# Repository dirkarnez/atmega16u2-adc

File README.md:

atmega16u2-adc
==============
- https://github.com/dirkarnez/ringbuffer
- https://github.com/dirkarnez/lufa-playground

### Datasheet
- https://ww1.microchip.com/downloads/en/DeviceDoc/doc7799.pdf

### Notes
- [Gammon Forum : Electronics : Microprocessors : How to make an Arduino-compatible minimal board](https://www.gammon.com.au/forum/?id=11637)
- [Gammon Forum : Electronics : Microprocessors : Minimal circuit for Atmega328 processor (shows wire-wrapping)](https://www.gammon.com.au/forum/?id=11109)
- `avrdude -p m328p -P /dev/ttyACM0 -c avrisp -b 19200 -U flash:w:release.hex`
- `"%LOCALAPPDATA%\Arduino15\packages\arduino\tools\avrdude\6.3.0-arduino17/bin/avrdude" "-C%LOCALAPPDATA%\Arduino15\packages\arduino\tools\avrdude\6.3.0-arduino17/etc/avrdude.conf" -v -p m16u2 -c arduino -PCOM5 -b19200 -U flash:w:Keyboard.hex:i -F -D`
- datasheet
  - `PDO, SPI Serial Programming Data Output. During Serial Program Downloading, this pin is used as data output line for the AT90USB82/162. `

### Bootloader
- [Pro Micro & Fio V3 Hookup Guide - SparkFun Learn](https://learn.sparkfun.com/tutorials/pro-micro--fio-v3-hookup-guide/troubleshooting-and-faq)
- [Installing an Arduino Bootloader - SparkFun Learn](https://learn.sparkfun.com/tutorials/installing-an-arduino-bootloader)
### Reference
- [Arduino入門教學(17) – 如何用 Arduino 燒錄 AVR 晶片 (作者：Cooper Maa)](http://programmermagazine.github.io/201405/htm/article1.html)
- [**Arduino 烧录 Boot Loader | 米米的博客**](https://zhangshuqiao.org/2019-10/Arduino%E7%83%A7%E5%BD%95Boot%20Loader/)
- [analogRead() - Arduino Reference](https://www.arduino.cc/reference/en/language/functions/analog-io/analogread/)
- https://github.com/arduino/ArduinoCore-avr/blob/master/firmwares/atmegaxxu2/arduino-usbserial/Arduino-usbserial-atmega16u2-Uno-Rev3.hex
  - `avrdude -p at90usb82 -F -P usb -c avrispmkii -U flash:w:UNO-dfu_and_usbserial_combined.hex -U lfuse:w:0xFF:m -U hfuse:w:0xD9:m -U efuse:w:0xF4:m -U lock:w:0x0F:m`
- https://github.com/arduino/ArduinoCore-avr/tree/master/firmwares/arduinoISP
  - https://github.com/arduino/ArduinoCore-avr/tree/master/firmwares/atmegaxxu2
- [用 AVR 做 USB 應用的考察 | Kalan's Blog](https://blog.kalan.dev/posts/2021-11-24-avr-usb-capability)
- [Arduino ATmega16U2 编译 LUFA_arduino mega16u2 源码-CSDN博客](https://blog.csdn.net/wowocpp/article/details/80626065)

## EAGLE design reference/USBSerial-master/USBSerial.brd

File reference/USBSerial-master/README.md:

# Freetronics USB to Serial converter

Can also be used as an atmega16u2 breakout/development board.

For full details see [http://freetronics.com/usbserial](http://freetronics.com/usbserial)

[View Schematic as PDF](https://github.com/freetronics/USBSerial/raw/master/USBSerial.pdf)

Design (C) 2013 Freetronics Pty Ltd
Published under the [TAPR Open Hardware License](http://tapr.org/ohl)

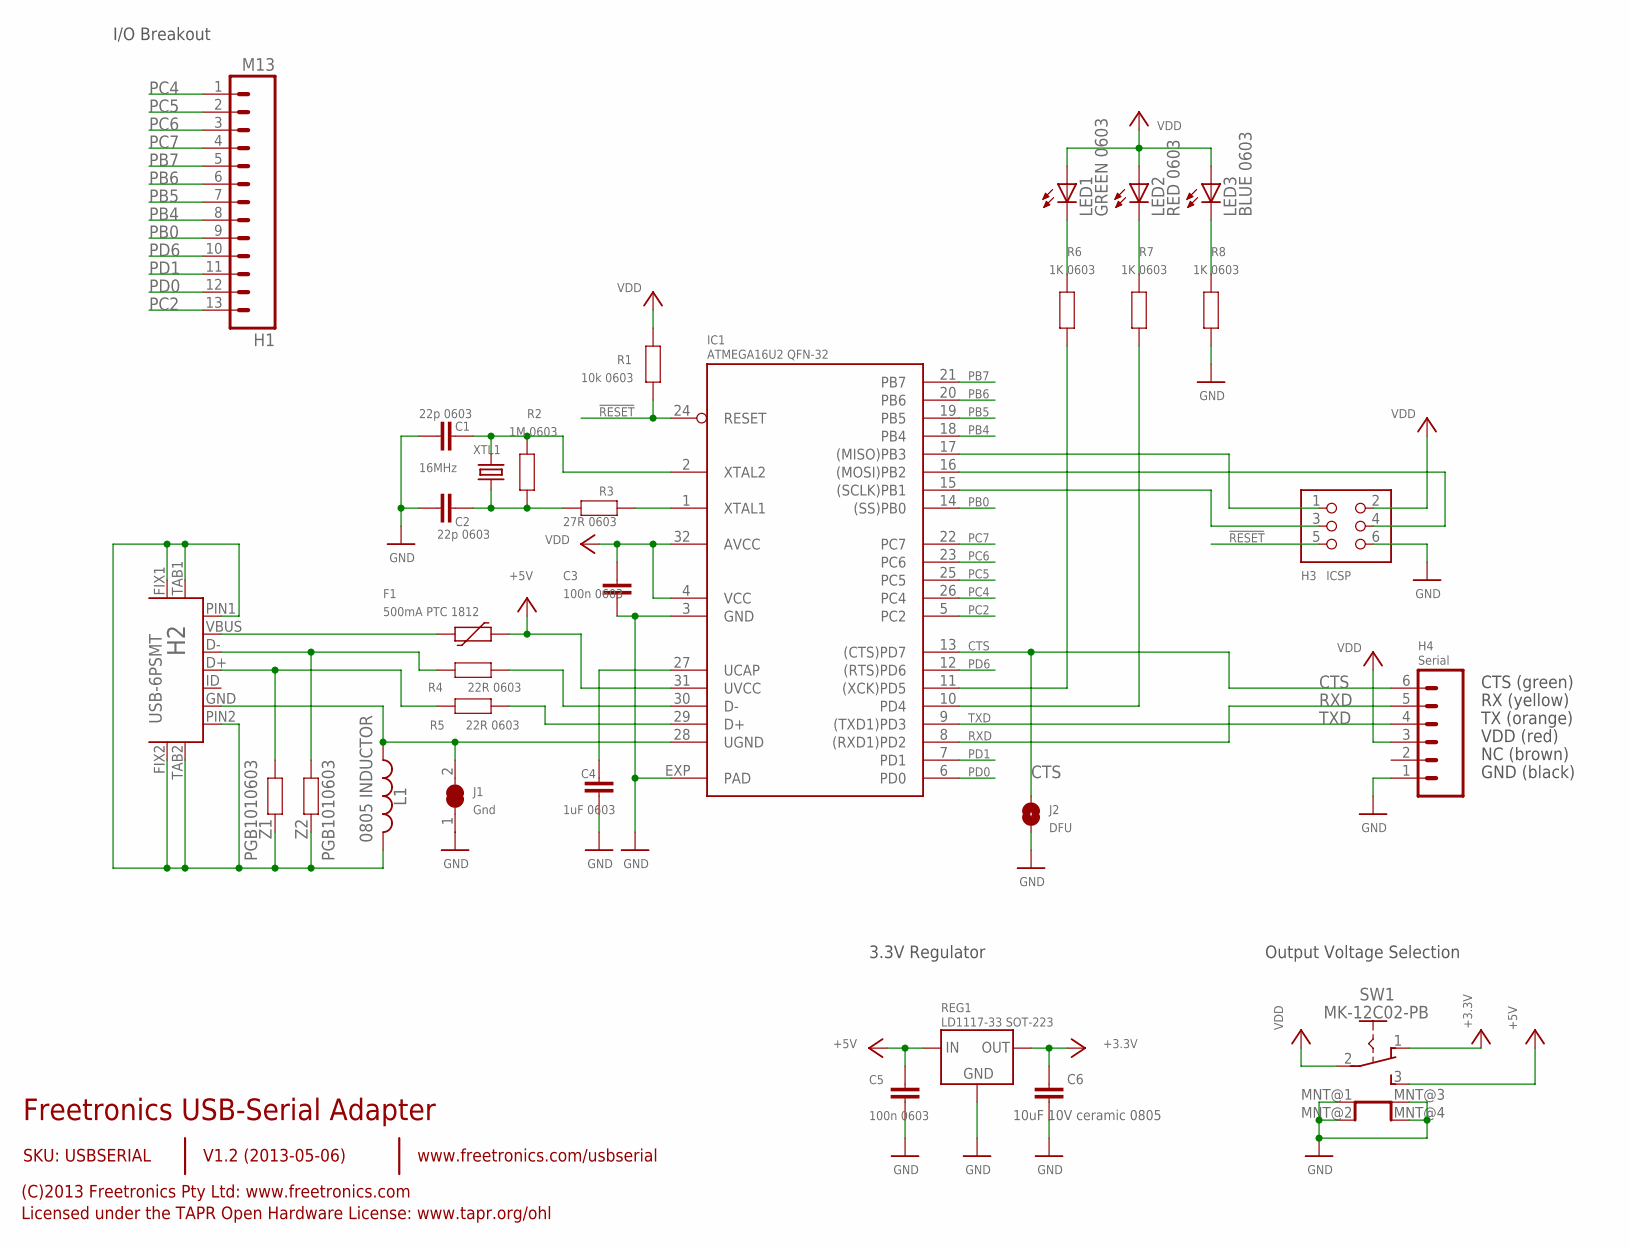
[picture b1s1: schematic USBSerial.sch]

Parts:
C1, C2: 22p 0603; 0603
C3, C5: 100n 0603; 0603
C4: 1uF 0603; 0603
C6: 10uF 10V ceramic 0805; C0805
F1: 500mA PTC 1812; 1812
H1: M13; 1X13
H2: USB-6PSMT; USB-MICROB-MB05PMXX
H3: ICSP; HEADER_2X3
H4: Serial; 1X06
IC1: ATMEGA16U2 QFN-32; ATMEL_QFN32
J1: Gnd; SJC
J2: DFU; SJ
L1: 0805 INDUCTOR; 0805-LARGE
LED1: GREEN 0603; LED-0603
LED2: RED 0603; LED-0603
LED3: BLUE 0603; LED-0603
R1: 10k 0603; 0603
R2: 1M 0603; 0603
R3: 27R 0603; 0603
R4, R5: 22R 0603; 0603
R6, R7, R8: 1K 0603; 0603
REG1: LD1117-33 SOT-223; SOT-223
SW1: MK-12C02-PB; MK-12C02
XTL1: 16MHz; HC49U-V
Z1, Z2: PGB1010603; 0603

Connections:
!RESET: H3.5, IC1.24 (RESET), R1.1
+3V3: C6.1, REG1.2 (OUT), REG1.4 (OUT), SW1.1 (A)
+5V: C5.1, F1.2, IC1.31 (UVCC), REG1.3 (IN), SW1.3 (B)
CTS: H4.6, IC1.13 ((CTS)PD7), J2.2
GND: C1.1, C2.1, C3.2, C4.2, C5.2, C6.2, H3.6, H4.1, IC1.3 (GND), IC1.EXP (PAD), J1.1, J2.1, R8.1, REG1.1 (GND), SW1.MNT@1 (MNT), SW1.MNT@2 (MNT), SW1.MNT@3 (MNT), SW1.MNT@4 (MNT)
MISO: H3.1, IC1.17 ((MISO)PB3)
MOSI: H3.4, IC1.16 ((MOSI)PB2)
unnamed: H2.GND, IC1.28 (UGND), J1.2, L1.1
unnamed: IC1.1 (XTAL1), R3.1
unnamed: LED1.C, R6.2
unnamed: LED2.C, R7.2
unnamed: H2.FIX1, H2.FIX2, H2.PIN1, H2.PIN2, H2.TAB1, H2.TAB2, L1.2, Z1.2, Z2.2
unnamed: LED3.C, R8.2
unnamed: H2.D+, R5.2, Z1.1
unnamed: H2.D-, R4.2, Z2.1
unnamed: C1.2, IC1.2 (XTAL2), R2.2, XTL1.2
unnamed: C2.2, R2.1, R3.2, XTL1.1
unnamed: F1.1, H2.VBUS
unnamed: C4.1, IC1.27 (UCAP)
PB0: H1.9, IC1.14 ((SS)PB0)
PB4: H1.8, IC1.18 (PB4)
PB5: H1.7, IC1.19 (PB5)
PB6: H1.6, IC1.20 (PB6)
PB7: H1.5, IC1.21 (PB7)
PC2: H1.13, IC1.5 (PC2)
PC4: H1.1, IC1.26 (PC4)
PC5: H1.2, IC1.25 (PC5)
PC6: H1.3, IC1.23 (PC6)
PC7: H1.4, IC1.22 (PC7)
PD0: H1.12, IC1.6 (PD0)
PD1: H1.11, IC1.7 (PD1)
PD6: H1.10, IC1.12 ((RTS)PD6)
RD+: IC1.29 (D+), R5.1
RD-: IC1.30 (D-), R4.1
RXD: H4.5, IC1.8 ((RXD1)PD2)
RXLED: IC1.10 (PD4), R7.1
SCK: H3.3, IC1.15 ((SCLK)PB1)
TXD: H4.4, IC1.9 ((TXD1)PD3)
TXLED: IC1.11 ((XCK)PD5), R6.1
VDD: C3.1, H3.2, H4.3, IC1.4 (VCC), IC1.32 (AVCC), LED1.A, LED2.A, LED3.A, R1.2, SW1.2 (COM)

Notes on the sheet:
Freetronics USB-Serial Adapter
V1.2 (2013-05-06)
SKU: USBSERIAL
(C)2013 Freetronics Pty Ltd: www.freetronics.com
Licensed under the TAPR Open Hardware License: www.tapr.org/ohl
www.freetronics.com/usbserial
CTS (green)
RX (yellow)
TX (orange)
VDD (red)
NC (brown)
GND (black)
Output Voltage Selection
3.3V Regulator
I/O Breakout

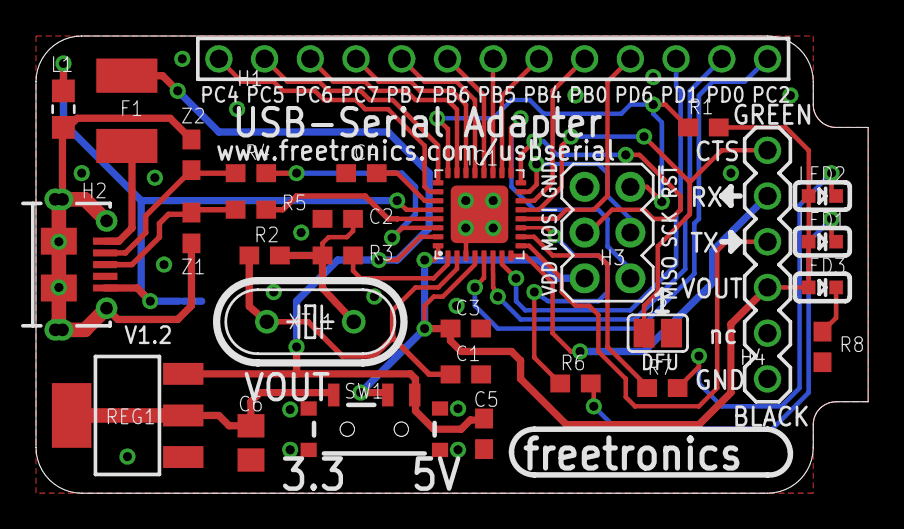
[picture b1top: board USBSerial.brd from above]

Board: 2 copper layers, 46.2 x 25.4 mm, 31 parts (1 on the bottom side), 40 nets.

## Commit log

2023-10-25 - upload files
2023-11-14 - add README.md
2023-12-08 - updat\e README.md
2024-01-02 - update README.md
2024-03-18 - add burn.cmd
2024-03-18 - add burn-from-youtube.cmd
2024-04-03 -update README.md
